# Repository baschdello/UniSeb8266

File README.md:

# UniSeb8266
Universal Sensorboard with ESP8266.

## Usage
### Tasmota
UniSeb8266 is designed to operate with Tasmota. Use the following template string:
```
{"NAME":"UniSeb8266","GPIO":[640,0,608,0,352,1312,0,0,0,1760,1,1728,1,0],"FLAG":0,"BASE":18}
```
### Power sources
There are different options to power the board:
| power source           | SJ1 jumper position |
| ---------------------- | ------------------- |
| HLK-PM01 230V-Module   | 'module'            |
| RT9400 PoE-Module      | 'module'            |
| 5V connector           | 'connector'         |
| D1-Mini USB connector  | no jumper required  |

### 3-pin connector J1
Use SJ2 to change usage of pin2:
| pin 2 utilization | SJ2 jumper position |
| ----------------- | ------------------- |
| 3.3V              | '3V3'               |
| gpio D5           | 'D5'                |

Pin3 is fixed to D0.

## Examples
PM sensor mounted on diy box
<br>

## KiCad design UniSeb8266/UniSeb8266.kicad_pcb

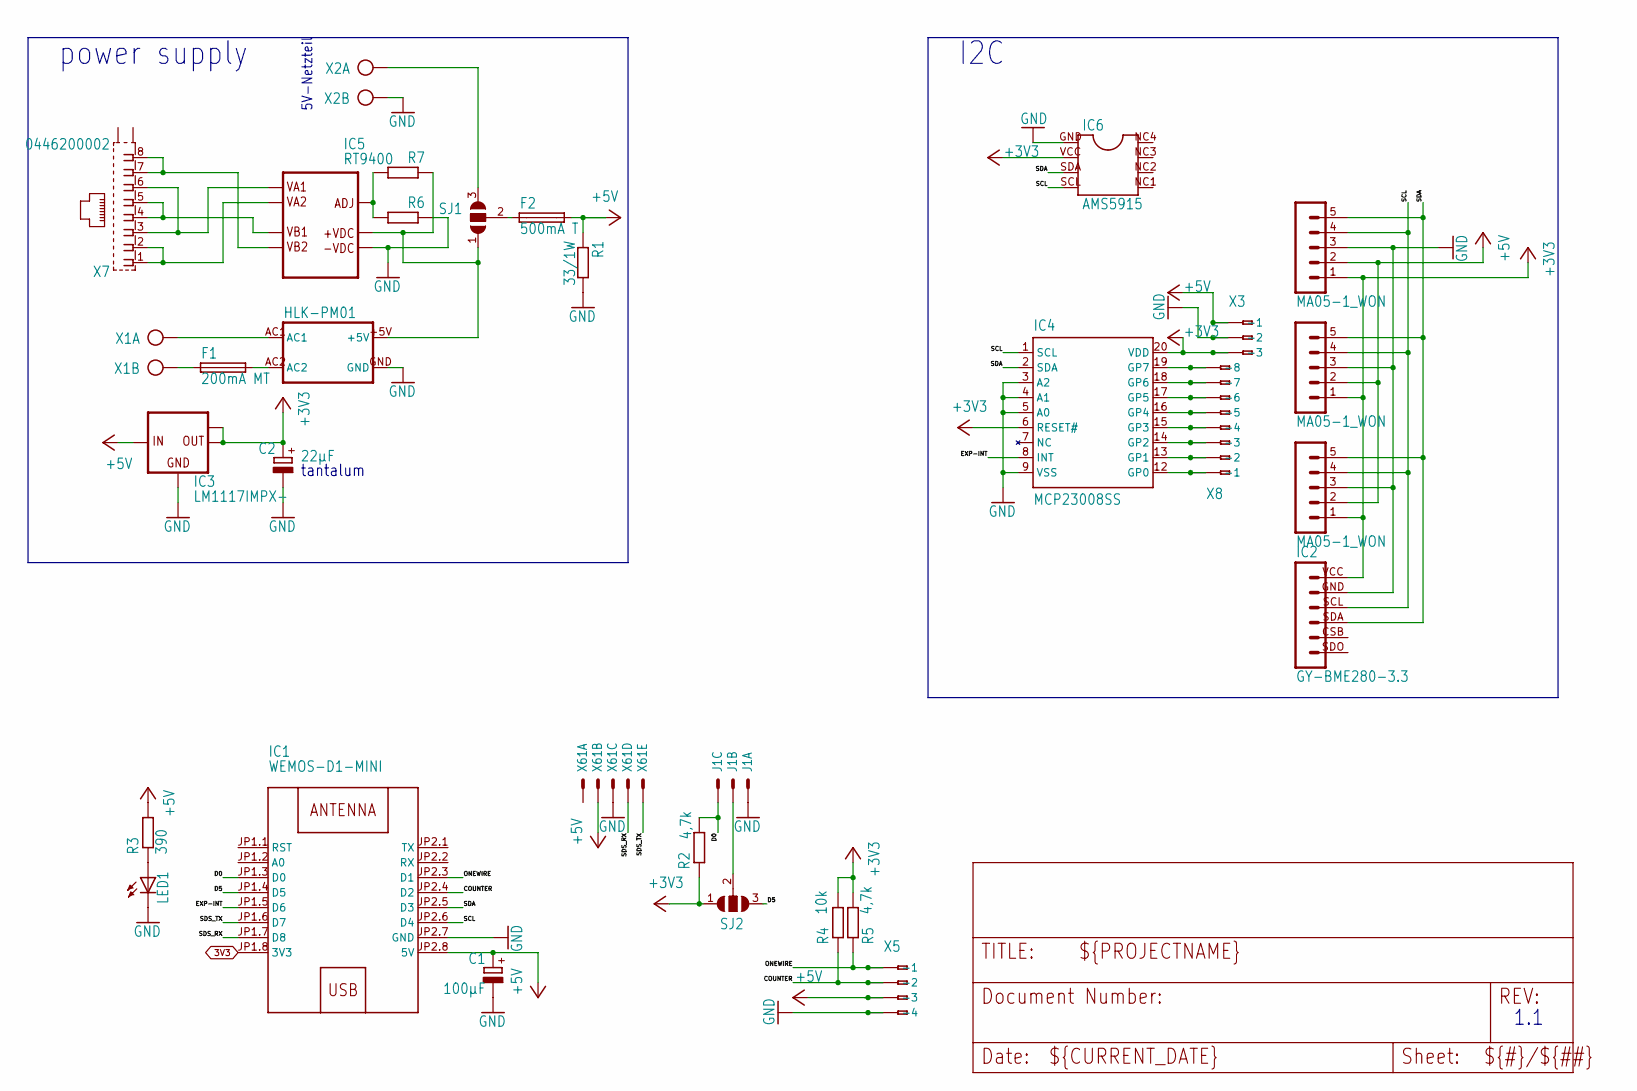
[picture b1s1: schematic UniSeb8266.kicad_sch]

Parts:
C1: 100µF; E2,5-6
C2: 22µF; E2,5-6
F1: 200mA MT; TR5
F2: 500mA T; TR5
I2C-1, I2C-2, I2C-3: MA05-1_WON
IC1: WEMOS-D1-MINI
IC2: GY-BME280-3.3
IC3: LM1117IMPX-; SOT223
IC4: MCP23008SS; SSOP20
IC5: RT9400
IC6: AMS5915
J1: 22-?-0327-2031; 6410-03
LED1: LED3MM
R1: 33/1W; P0613V
R2: 4,7k; R_0603_1608Metric; LCSC C23162
R3: 390; R1206
R4: 10k; R1206
R5: 4,7k; R1206
R6, R7: R-EU_R1206; R1206
SJ1, SJ2: SJ2W; SJ_2
U$2: HLK-PM01
X1, X2: AK500/2; AK500_2
X3: 233-503
X5: 233-504
X7: 0446200002
X8: 233-508
X61: JST-XH-05-PIN-LONG-PAD; JST-XH-05-PACKAGE-LONG-PAD

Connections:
3V3: IC1.JP1.8 (3V3)
+3V3: C2.+, I2C-1.1, I2C-2.1, I2C-3.1, IC2.VCC, IC3.2 (OUT), IC3.TAB (OUT1), IC4.6 (RESET#), IC4.20 (VDD), IC6.VCC (2), R2.1, R4.2, R5.2, SJ2.1, X3.A3 (-3), X3.B3 (B-3)
+5V: C1.+, F2.2, I2C-1.2, I2C-2.2, I2C-3.2, IC1.JP2.8 (5V), IC3.3 (IN), R1.1, R3.2, X3.A1 (-1), X3.B1 (B-1), X5.A3 (-3), X5.B3 (B-3), X61.2 (S)
/COUNTER: IC1.JP2.4 (D2), R4.1, X5.A2 (-2), X5.B2 (B-2)
/D0: IC1.JP1.3 (D0), J1.3 (S), R2.2
/D5: IC1.JP1.4 (D5), SJ2.3
/EXP-INT: IC1.JP1.5 (D6), IC4.8 (INT)
/ONEWIRE: IC1.JP2.3 (D1), R5.1, X5.A1 (-1), X5.B1 (B-1)
/SCL: I2C-1.4, I2C-2.4, I2C-3.4, IC1.JP2.6 (D4), IC2.SCL, IC4.1 (SCL), IC6.SCL (4)
/SDA: I2C-1.5, I2C-2.5, I2C-3.5, IC1.JP2.5 (D3), IC2.SDA, IC4.2 (SDA), IC6.SDA (3)
/SDS_RX: IC1.JP1.7 (D8), X61.4 (S)
/SDS_TX: IC1.JP1.6 (D7), X61.5 (S)
GND: C1.-, C2.-, I2C-1.3, I2C-2.3, I2C-3.3, IC1.JP2.7 (GND), IC2.GND, IC3.1 (GND), IC4.3 (A2), IC4.4 (A1), IC4.5 (A0), IC4.9 (VSS), IC5.P$5 (-VDC), IC6.GND (1), J1.1 (S), LED1.K (C), R1.2, R6.1, U$2.GND, X2.2 (KL), X3.A2 (-2), X3.B2 (B-2), X5.A4 (-4), X5.B4 (B-4), X61.3 (S)
unnamed: F1.2, U$2.AC2
unnamed: F2.1, SJ1.2
unnamed: IC4.12 (GP0), X8.A1 (-1), X8.B1 (B-1)
unnamed: IC4.13 (GP1), X8.A2 (-2), X8.B2 (B-2)
unnamed: IC4.14 (GP2), X8.A3 (-3), X8.B3 (B-3)
unnamed: IC4.15 (GP3), X8.A4 (-4), X8.B4 (B-4)
unnamed: IC4.16 (GP4), X8.A5 (-5), X8.B5 (B-5)
unnamed: IC4.17 (GP5), X8.A6 (-6), X8.B6 (B-6)
unnamed: IC4.18 (GP6), X8.A7 (-7), X8.B7 (B-7)
unnamed: IC4.19 (GP7), X8.A8 (-8), X8.B8 (B-8)
unnamed: IC5.P$6 (+VDC), R7.1, SJ1.1, U$2.+5V
unnamed: IC5.P$7 (ADJ), R6.2, R7.2
unnamed: IC5.P$1 (VA1), X7.3, X7.6
unnamed: IC5.P$2 (VA2), X7.1, X7.2
unnamed: IC5.P$3 (VB1), X7.4, X7.5
unnamed: IC5.P$4 (VB2), X7.7, X7.8
unnamed: J1.2 (S), SJ2.2
unnamed: LED1.A, R3.1
unnamed: U$2.AC1, X1.1 (KL)
unnamed: F1.1, X1.2 (KL)
unnamed: SJ1.3, X2.1 (KL)

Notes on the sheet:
I2C
5V-Netzteil
tantalum
power supply
1.1

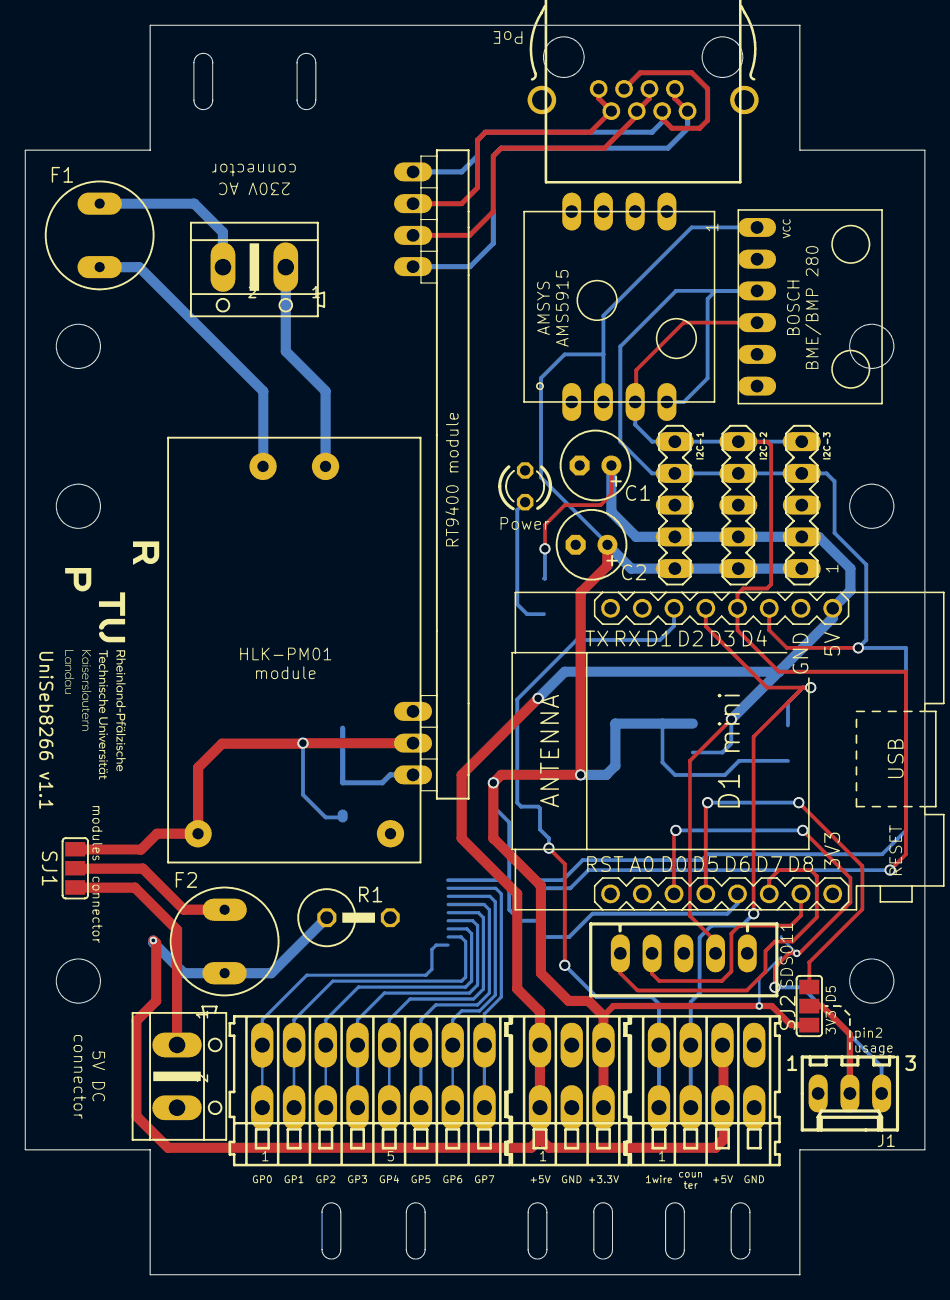
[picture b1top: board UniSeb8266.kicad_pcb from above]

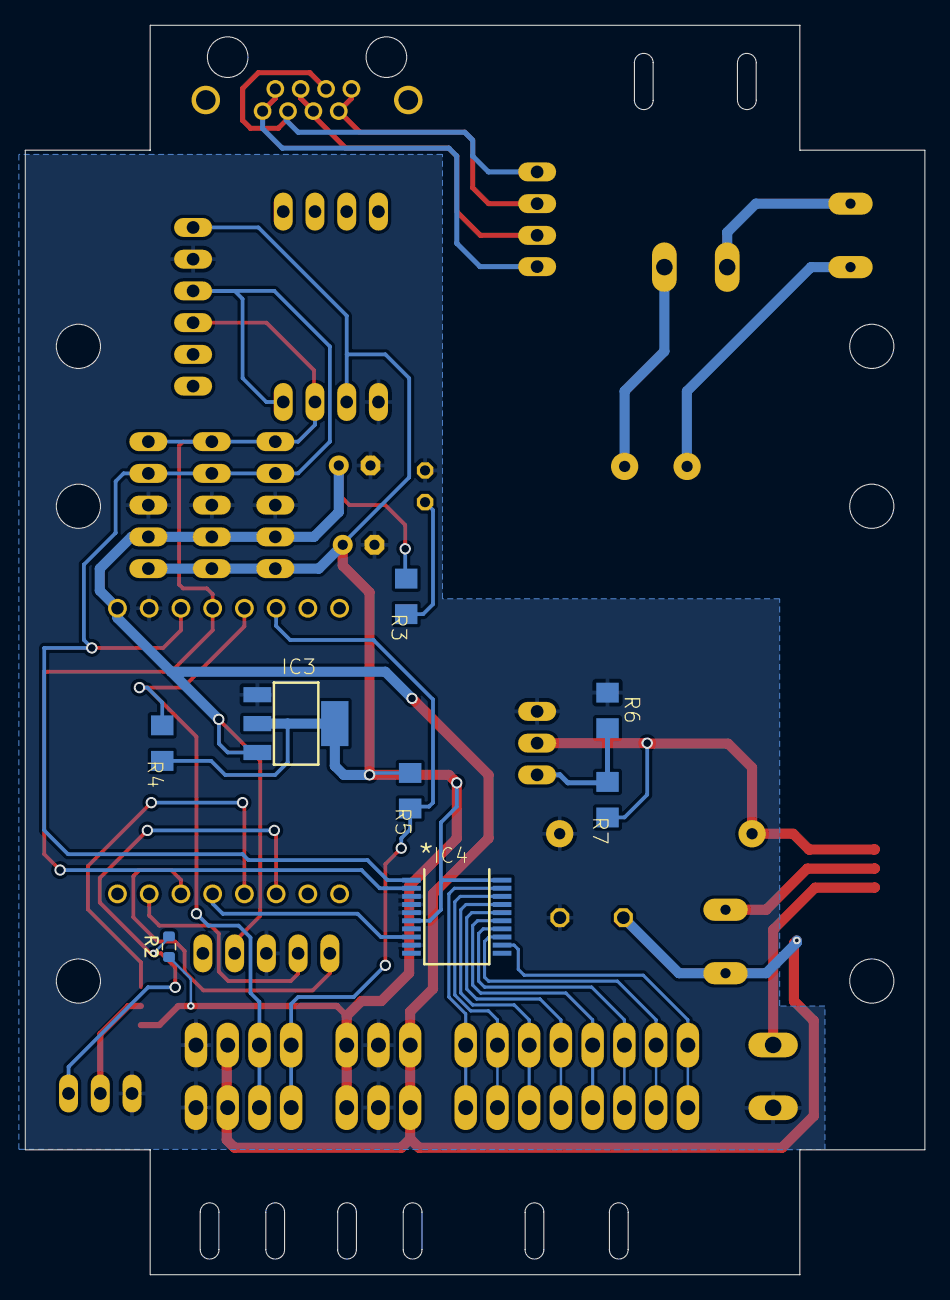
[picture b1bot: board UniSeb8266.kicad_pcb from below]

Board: 2 copper layers, 72.0 x 100.0 mm, 32 parts (8 on the bottom side), 33 nets.

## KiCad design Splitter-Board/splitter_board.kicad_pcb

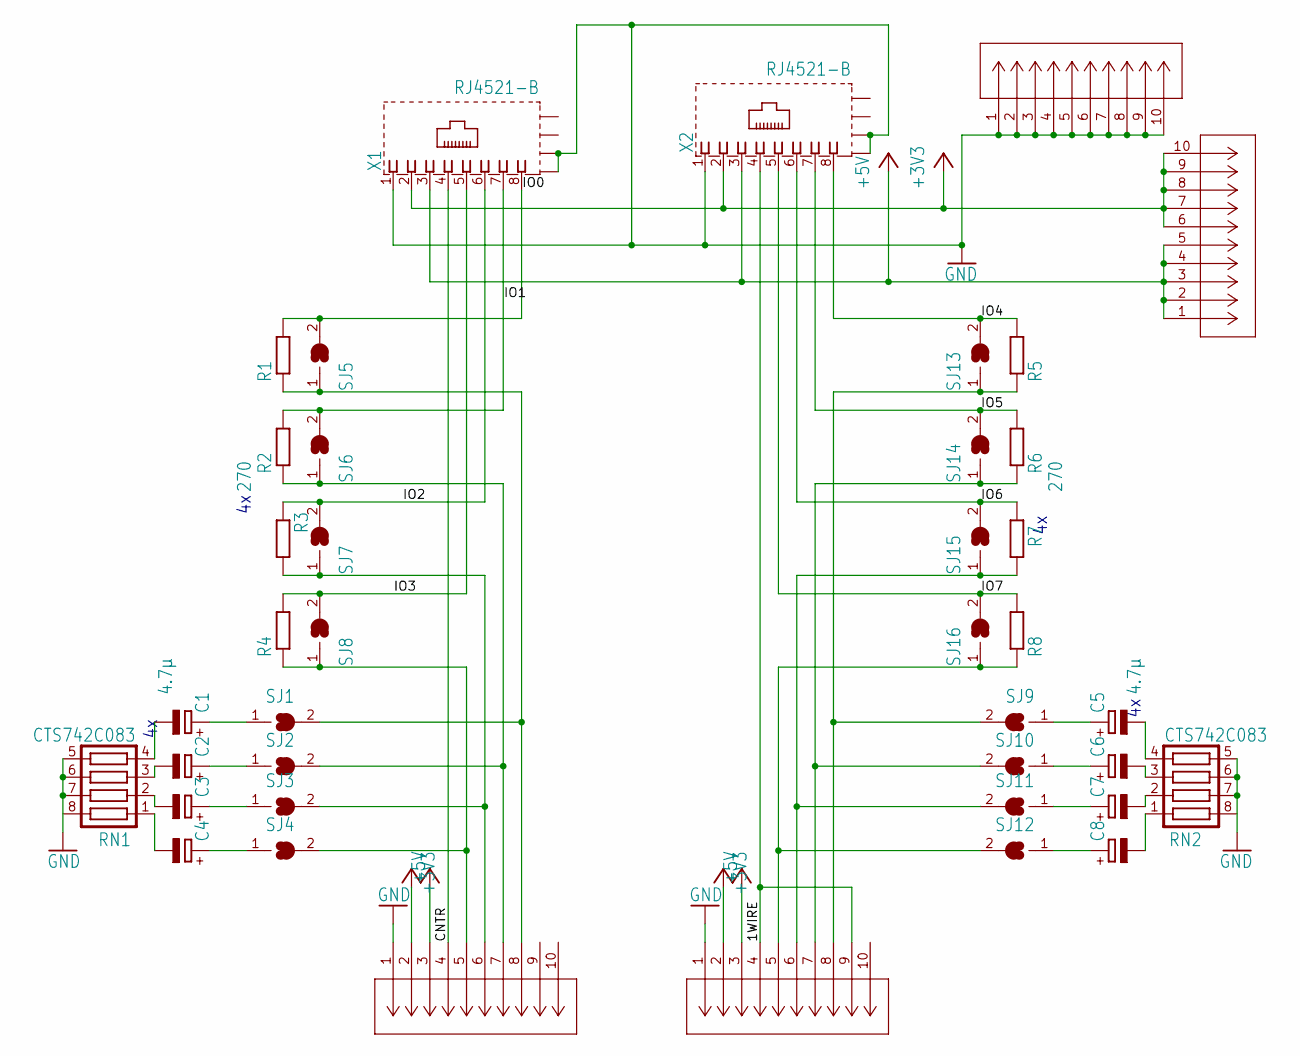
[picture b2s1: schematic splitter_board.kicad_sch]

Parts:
C1, C2, C3, C4, C5, C6, C7, C8: 4.7µ; A_3216-18R; JLC C110309
J1, J2, J3, J4: 250-410; CONN_250-410_WAG
R1, R2, R3, R4, R5, R6, R7, R8: 270; R0805
RN1, RN2: CTS742C083
SJ1, SJ2, SJ3, SJ4, SJ5, SJ6, SJ7, SJ8, SJ9, SJ10, SJ11, SJ12, SJ13, SJ14, SJ15, SJ16: SJ
X1, X2: RJ4521-B; RJ45-SHIELD1

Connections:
1WIRE: J2.4, J2.9, X2.4
+3V3: J1.2, J2.2, J4.6, J4.7, J4.8, J4.9, J4.10, X1.2, X2.2
+5V: J1.3, J2.3, J4.1, J4.2, J4.3, J4.4, J4.5, X1.3, X2.3
CNTR: J1.4, X1.4
GND: J1.1, J2.1, J3.1, J3.2, J3.3, J3.4, J3.5, J3.6, J3.7, J3.8, J3.9, J3.10, RN1.5, RN1.6, RN1.7, RN1.8, RN2.5, RN2.6, RN2.7, RN2.8, X1.1, X1.S1 (S@1), X1.S2 (S@2), X2.1, X2.S1 (S@1), X2.S2 (S@2)
IO0: R1.2, SJ5.2, X1.8
IO1: R2.2, SJ6.2, X1.7
IO2: R3.2, SJ7.2, X1.6
IO3: R4.2, SJ8.2, X1.5
IO4: R5.2, SJ13.2, X2.8
IO5: R6.2, SJ14.2, X2.7
IO6: R7.2, SJ15.2, X2.6
IO7: R8.2, SJ16.2, X2.5
unnamed: C8.-, RN2.1
unnamed: C7.-, RN2.2
unnamed: C6.-, RN2.3
unnamed: C5.-, RN2.4
unnamed: C4.-, RN1.1
unnamed: C3.-, RN1.2
unnamed: C2.-, RN1.3
unnamed: C1.-, RN1.4
unnamed: C5.+, SJ9.1
unnamed: C6.+, SJ10.1
unnamed: C7.+, SJ11.1
unnamed: C8.+, SJ12.1
unnamed: J2.8, R5.1, SJ9.2, SJ13.1
unnamed: J2.7, R6.1, SJ10.2, SJ14.1
unnamed: J2.6, R7.1, SJ11.2, SJ15.1
unnamed: J2.5, R8.1, SJ12.2, SJ16.1
unnamed: C1.+, SJ1.1
unnamed: C2.+, SJ2.1
unnamed: C3.+, SJ3.1
unnamed: C4.+, SJ4.1
unnamed: J1.7, R2.1, SJ2.2, SJ6.1
unnamed: J1.8, R1.1, SJ1.2, SJ5.1
unnamed: J1.6, R3.1, SJ3.2, SJ7.1
unnamed: J1.5, R4.1, SJ4.2, SJ8.1

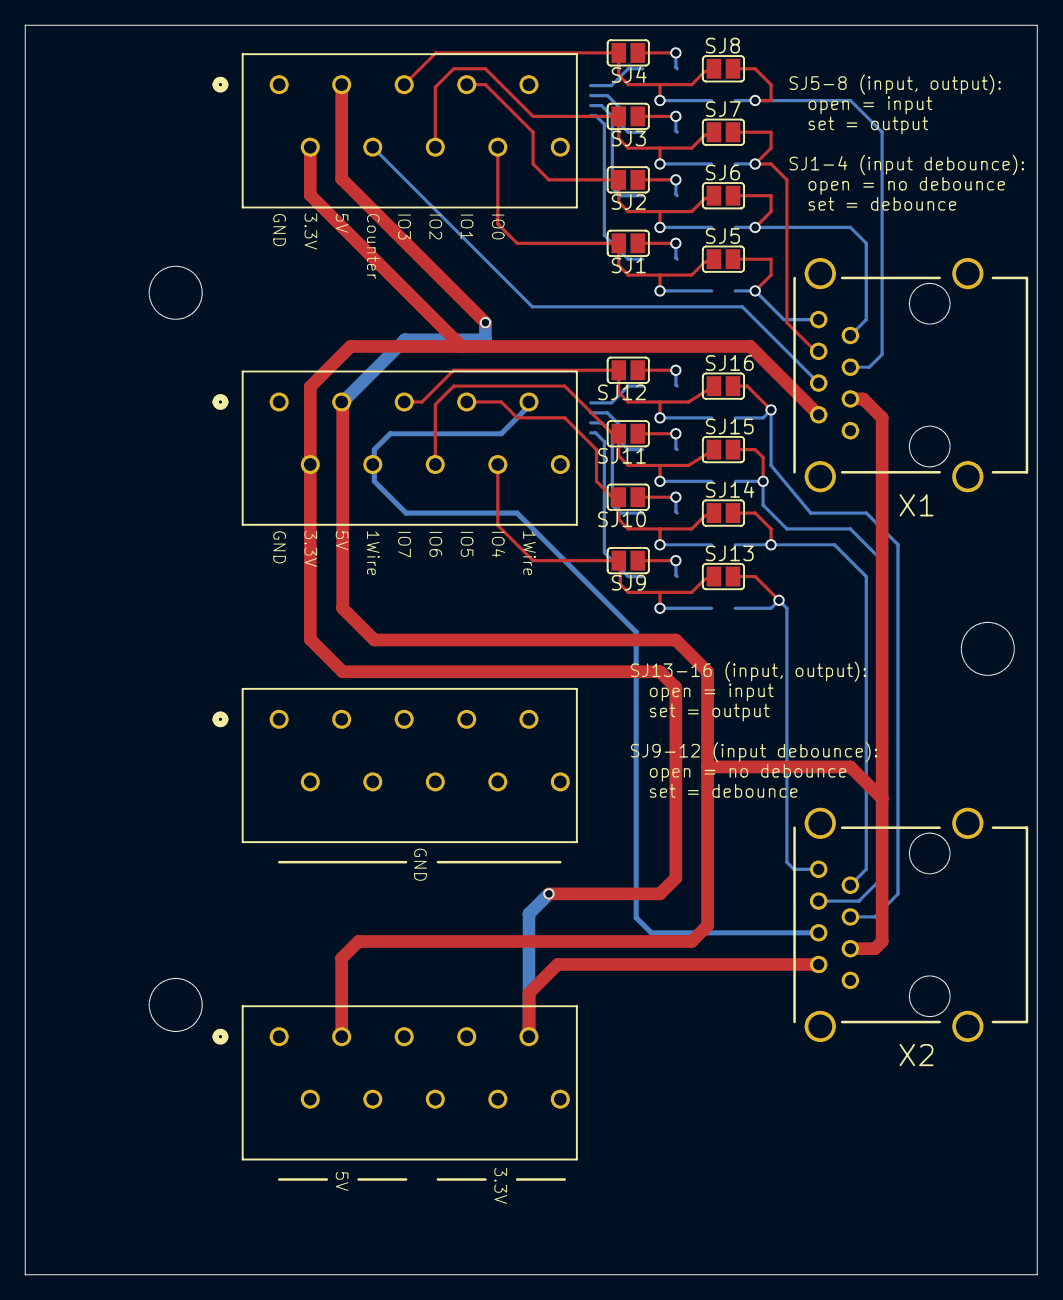
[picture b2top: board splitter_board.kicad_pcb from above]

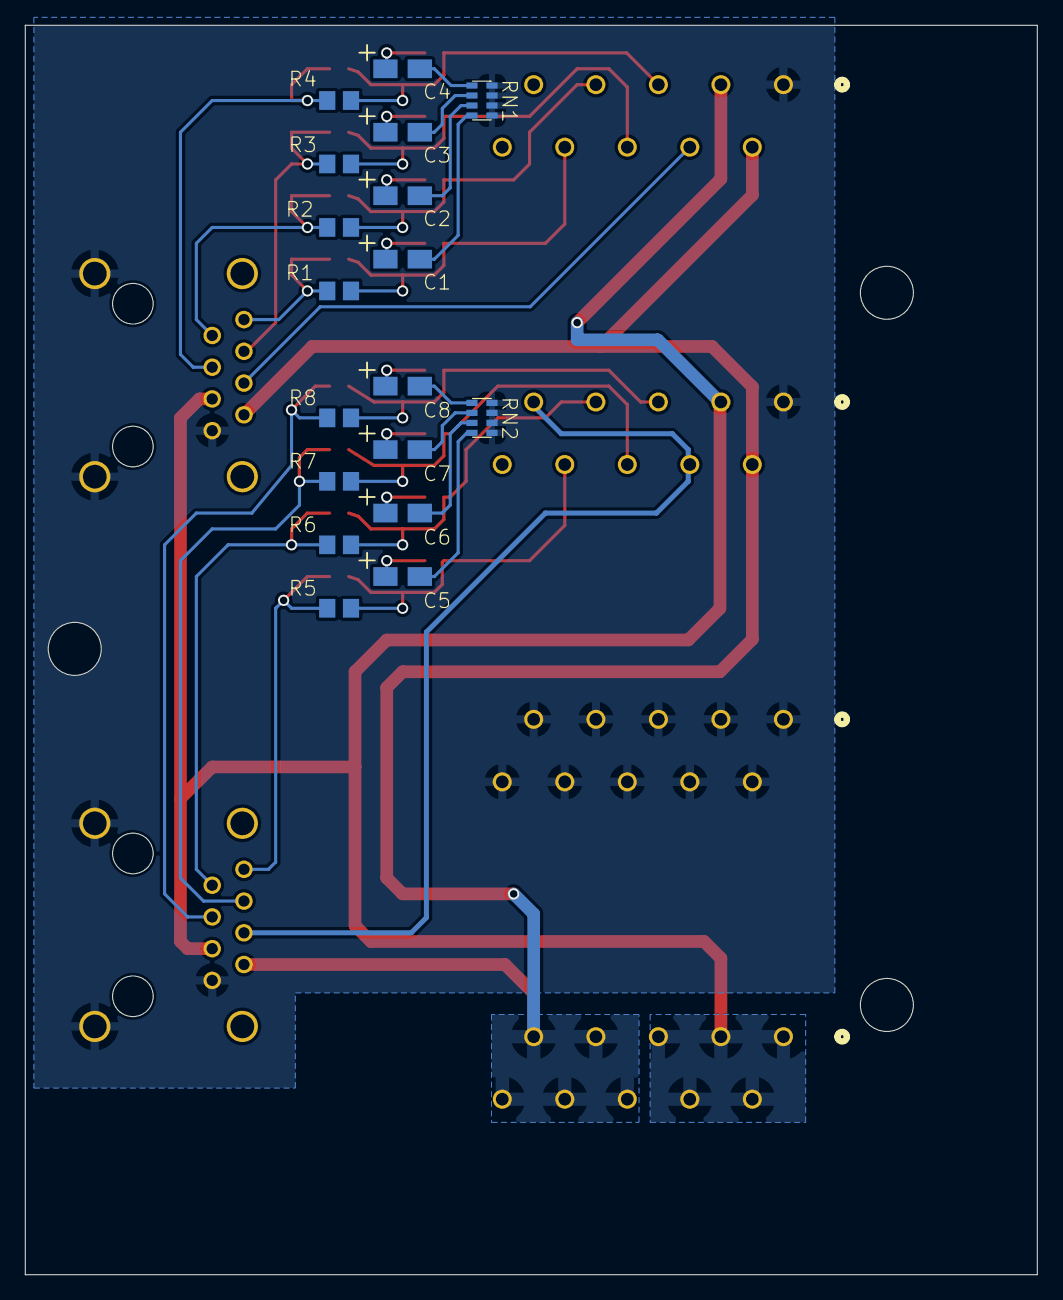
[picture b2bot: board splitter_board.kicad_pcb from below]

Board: 2 copper layers, 81.0 x 100.0 mm, 40 parts (18 on the bottom side), 37 nets.

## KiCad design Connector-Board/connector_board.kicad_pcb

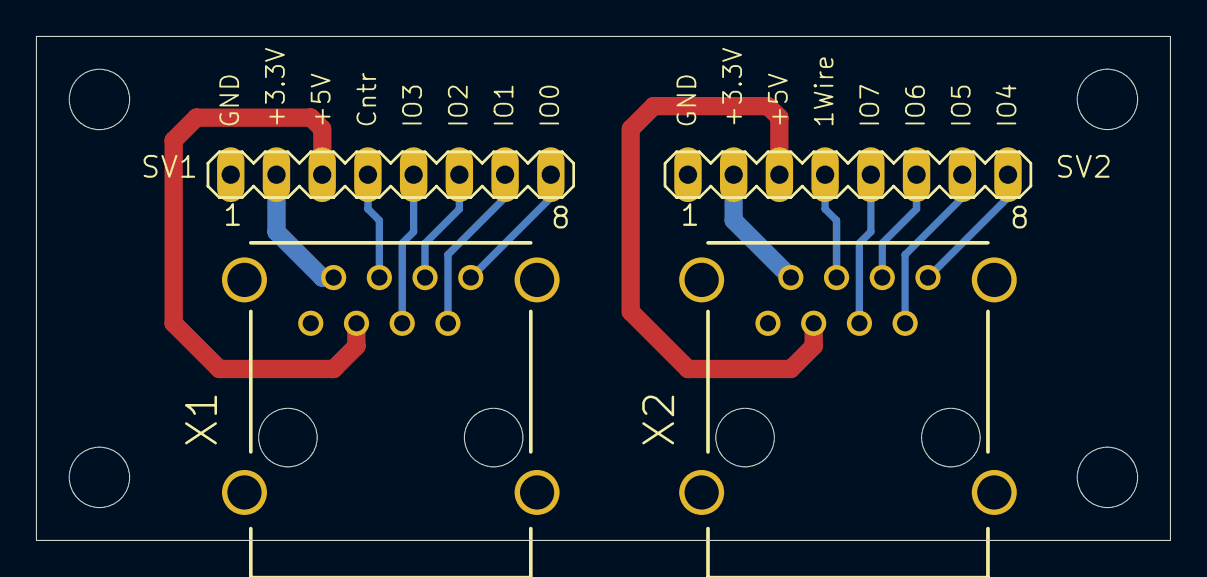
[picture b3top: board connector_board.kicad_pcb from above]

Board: 2 copper layers, 63.0 x 28.0 mm, 4 parts (0 on the bottom side), 15 nets.

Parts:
SV1, SV2: MA08-1
X1, X2: RJ45-6L21-B; RJ45-SHIELD1

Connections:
GND: SV1.1, SV2.1, X1.1, X1.S1, X1.S2, X1.S3, X1.S4, X2.1, X2.S1, X2.S2, X2.S3, X2.S4
unnamed: SV1.3, X1.3
unnamed: SV1.4, X1.4
unnamed: SV1.5, X1.5
unnamed: SV1.6, X1.6
unnamed: SV1.7, X1.7
unnamed: SV1.8, X1.8
unnamed: SV2.3, X2.3
unnamed: SV2.4, X2.4
unnamed: SV2.5, X2.5
unnamed: SV2.6, X2.6
unnamed: SV2.7, X2.7
unnamed: SV2.8, X2.8
unnamed: SV1.2, X1.2
unnamed: SV2.2, X2.2

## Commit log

2020-01-28 Changed the fixed voltage regulator to AMS1117/LM1117 and the output capacitor.
2020-02-09 Changed placement of IC3 to bottom layer.
2021-06-11 rear/front connector board
2022-07-11 added PCBs for extern IO-connections
2024-06-06 migration to KiCad
2024-06-06 cleanup
2024-06-06 changed name of SJ2 -> SJ1
2024-06-06 added SJ2 to change pin-2 usage of "Molex KK 254" connector (3.3V or D5)
2024-06-06 added R2 pullup for pin3 of J1
